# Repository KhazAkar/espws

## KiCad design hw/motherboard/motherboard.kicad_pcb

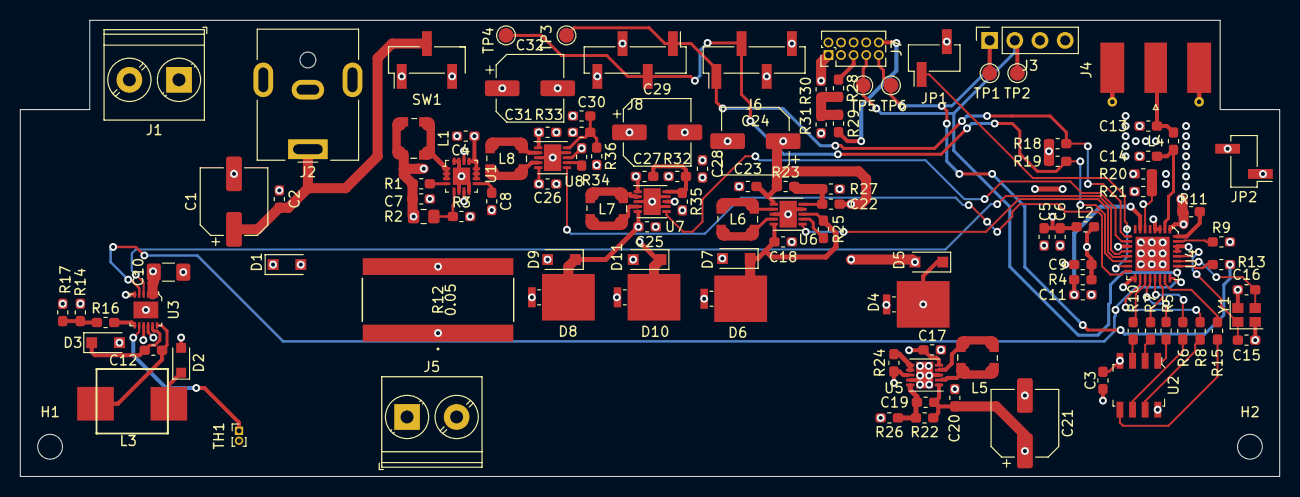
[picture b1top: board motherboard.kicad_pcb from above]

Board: 4 copper layers, 127.0 x 46.0 mm, 116 parts (0 on the bottom side), 75 nets.

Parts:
C1, C21, C24, C29, C32: 22uF; CP_Elec_6.3x5.4
C2, C3, C6, C11: 100nF; C_0603_1608Metric_Pad1.05x0.95mm_HandSolder
C4, C5: 10uF; C_0603_1608Metric_Pad1.05x0.95mm_HandSolder
C7, C17, C18, C25, C26: 22uF; C_0603_1608Metric_Pad1.05x0.95mm_HandSolder
C8: 680pF; C_0603_1608Metric_Pad1.05x0.95mm_HandSolder
C9, C20, C23, C28, C31: 1uF; C_0603_1608Metric_Pad1.05x0.95mm_HandSolder
C10: 22uF; C_1206_3216Metric_Pad1.42x1.75mm_HandSolder
C12: 1uF/50V; C_0603_1608Metric_Pad1.05x0.95mm_HandSolder
C13: 2.4pF; C_0603_1608Metric_Pad1.05x0.95mm_HandSolder
C14: 3pF; C_0603_1608Metric_Pad1.05x0.95mm_HandSolder
C15, C16: 10pF; C_0603_1608Metric_Pad1.05x0.95mm_HandSolder
C19, C27: 4.7uF; C_0603_1608Metric_Pad1.05x0.95mm_HandSolder
C22, C30: 47pF; C_0603_1608Metric_Pad1.05x0.95mm_HandSolder
D1, D3, D5, D7, D9, D11: DB2W40300L; D_SOD-123F
D2: CMDSH2-4L; D_SOD-323_HandSoldering
D4, D6, D8, D10: UPS115UE3; D_Powermite2_AK
H1, H2: MountingHole; MountingHole_2.5mm
J1: Solar Panel; TerminalBlock_Phoenix_PT-1,5-2-5.0-H_1x02_P5.00mm_Horizontal
J2: 9V 3A; BarrelJack_CUI_PJ-063AH_Horizontal
J3: ESP8266 UART; PinSocket_1x04_P2.54mm_Vertical
J4: WiFi Antenna; SMA_Molex_73251-1153_EdgeMount_Horizontal
J5: LiFePO4; TerminalBlock_Phoenix_PT-1,5-2-5.0-H_1x02_P5.00mm_Horizontal
J6: BME280; PinHeader_1x04_P2.54mm_Vertical_SMD_Pin1Left
J7: PMS7003; PinHeader_2x05_P1.27mm_Vertical
J8: WIND; PinHeader_1x04_P2.54mm_Vertical_SMD_Pin1Left
JP1: Programming mode; PinHeader_1x02_P2.54mm_Vertical_SMD_Pin1Left
JP2: Reset; PinHeader_1x02_P2.54mm_Vertical_SMD_Pin1Left
L1, L5, L6, L7, L8: 2.2uH; L_Wuerth_WE-TPC-3816
L2: 4.3nH; L_0603_1608Metric_Pad1.05x0.95mm_HandSolder
L3: 5.6uH; SRP6540
L4: 2.2nH; L_0603_1608Metric_Pad1.05x0.95mm_HandSolder
R1, R20, R26, R27, R35, R36: 100k; R_0603_1608Metric_Pad1.05x0.95mm_HandSolder
R2: 1M07; R_0805_2012Metric_Pad1.15x1.40mm_HandSolder
R3, R22, R32: 180k; R_0603_1608Metric_Pad1.05x0.95mm_HandSolder
R4, R11, R28, R29: 10k; R_0603_1608Metric_Pad1.05x0.95mm_HandSolder
R5, R6, R7, R8, R10, R15: 200; R_0603_1608Metric_Pad1.05x0.95mm_HandSolder
R9: 12k; R_0603_1608Metric_Pad1.05x0.95mm_HandSolder
R12: 0.05; FCSL150R050FER
R13: 499; R_0603_1608Metric_Pad1.05x0.95mm_HandSolder
R14: 30k; R_0603_1608Metric_Pad1.05x0.95mm_HandSolder
R16: 223k; R_0603_1608Metric_Pad1.05x0.95mm_HandSolder
R17: 330k; R_0603_1608Metric_Pad1.05x0.95mm_HandSolder
R18, R19, R31: 2k; R_0603_1608Metric_Pad1.05x0.95mm_HandSolder
R21: 37k; R_0603_1608Metric_Pad1.05x0.95mm_HandSolder
R23, R33: 150k; R_0603_1608Metric_Pad1.05x0.95mm_HandSolder
R24, R25, R34: 4.7k; R_0603_1608Metric_Pad1.05x0.95mm_HandSolder
R30: 1k; R_0603_1608Metric_Pad1.05x0.95mm_HandSolder
SW1: Charge/Power; PinHeader_1x03_P2.54mm_Vertical_SMD_Pin1Left
TH1: 10k B=3380; PinHeader_1x02_P1.00mm_Vertical
TP1: U0TXD_Test; TestPoint_Pad_D1.5mm
TP2: U0RXD_Test; TestPoint_Pad_D1.5mm
TP3: SCL_TP; TestPoint_Pad_D1.5mm
TP4: SDA_TP; TestPoint_Pad_D1.5mm
TP5: DUST_RX_TP; TestPoint_Pad_D1.5mm
TP6: DUST_TX_TP; TestPoint_Pad_D1.5mm
U1: TPS62140A; VFQFN-16-1EP_3x3mm
U2: GD25Q32CSIGR; SOIC-8_W5.3mm
U3: LT3652EDD; DFN-12-1EP_3x3mm
U4: ESP8266EX; QFN-32-1EP_5x5mm
U5, U6, U7, U8: RT6150; DFN-10-1EP_3x3mm_P0.5mm_EP1.75x2.7mm
Y1: 40MHz±10ppm; Crystal_SMD_2520-4Pin_2.5x2.0mm

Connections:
5V6: C7.1, D5.2, D7.2, D9.2, D11.2, L1.2, R1.1, R2.1, U1.7, U1.14
+9V: D1.2, SW1.1
+9VA: C4.1, SW1.3, U1.10, U1.11, U1.12, U1.13
+12V: C10.1, D1.1, J1.1, U3.1, U3.2, U3.3
+BATT: D3.2, D4.2, D6.2, D8.2, D10.2, J5.1, R12.1, R14.1, R20.1, U3.9
ADC: R20.2, R21.1, U4.6
BME280_EN: U4.10, U7.6
BME280_SCL: J6.1, J8.1, R18.2, TP3.1, U4.9
BME280_SDA: J6.2, J8.2, R19.2, TP4.1, U4.14
BME280_VCC: C27.1, C28.1, C29.1, J6.3, R32.1, U7.1
DUST_3V3: R28.2, R29.2, R30.2, R31.1
DUST_EN: U4.13, U6.6
DUST_RX: J3.2, J7.7, TP2.1, TP5.1, U4.25
DUST_TX: J3.1, J7.9, R13.1, TP1.1, TP6.1
DUST_VCC: C22.1, C23.1, C24.1, J7.1, J7.2, R23.1, R30.1, U6.1
ESP_VCC: C3.2, C5.1, C6.1, C9.1, C19.1, C20.1, C21.1, J3.3, JP2.2, L2.1, L2.2, R4.1, R11.2, R18.1, R19.1, R22.1, U2.8, U4.1, U4.3, U4.4, U4.11, U4.17, U4.29, U4.30, U5.1
GND: C1.2, C2.2, C3.1, C4.2, C5.2, C6.2, C7.2, C8.2, C9.2, C10.2, C11.2, C13.2, C14.2, C15.2, C16.2, C17.2, C18.2, C20.2, C21.2, C23.2, C24.2, C25.2, C26.2, C28.2, C29.2, C31.2, C32.2, D2.2, J1.2, J2.2, J3.4, J4.2, J5.2, J6.4, J7.3, J7.4, J8.4, JP1.2, JP2.1, R3.2, R9.2, R17.2, R21.2, R26.2, R27.2, R31.2, R35.2, R36.2, TH1.2, U1.6, U1.8, U1.15, U1.16, U1.17, U2.4, U3.6, U3.13, U4.33, U5.3, U5.9, U5.11, U6.3, U6.9, U6.11, U7.3, U7.7, U7.9, U7.11, U8.3, U8.9, U8.11, Y1.2, Y1.4
unnamed: C1.1, C2.1, J2.1, SW1.2
unnamed: C8.1, U1.9
unnamed: C11.1, R4.2, U4.7
unnamed: C12.1, L3.1, U3.12
unnamed: C12.2, D3.1, U3.11
unnamed: C13.1, J4.1, L4.1
unnamed: C14.1, L4.2, U4.2
unnamed: C15.1, U4.28, Y1.1
unnamed: C16.1, U4.27, Y1.3
unnamed: C17.1, D4.1, D5.1, R24.1, U5.5, U5.8
unnamed: C18.1, D6.1, D7.1, R25.1, U6.5, U6.8
unnamed: C19.2, R22.2, R26.1, U5.10
unnamed: C22.2, R23.2, R27.1, U6.10
unnamed: C25.1, D8.1, D9.1, U7.5, U7.8
unnamed: C26.1, D10.1, D11.1, R34.1, U8.5, U8.8
unnamed: C27.2, R32.2, R35.1, U7.10
unnamed: C30.2, R33.2, R36.1, U8.10
unnamed: D2.1, L3.2
unnamed: J7.5, R28.1
unnamed: J7.10, R29.1
unnamed: L1.1, U1.1, U1.2, U1.3
unnamed: L5.1, U5.2
unnamed: L5.2, U5.4
unnamed: L6.1, U6.2
unnamed: L6.2, U6.4
unnamed: L7.1, U7.2
unnamed: L7.2, U7.4
unnamed: L8.1, U8.2
unnamed: L8.2, U8.4
unnamed: R1.2, U1.4
unnamed: R2.2, R3.1, U1.5
unnamed: R5.2, U4.20
unnamed: R6.2, U4.21
unnamed: R7.2, U4.22
unnamed: R8.2, U4.18
unnamed: R9.1, U4.31
unnamed: R10.2, U4.19
unnamed: R11.1, U4.32
unnamed: R12.2, U3.10
unnamed: R13.2, U4.26
unnamed: R14.2, R16.1, R17.1
unnamed: R15.2, U4.23
unnamed: R16.2, U3.7
unnamed: R24.2, U5.6, U5.7
unnamed: R25.2, U6.7
unnamed: R34.2, U8.7
unnamed: TH1.1, U3.8
PRG: JP1.1, U4.15
SD_CLK: R6.1, U2.6
SD_CMD: R5.1, U2.1
SD_D0: R7.1, U2.2
SD_D1: R15.1, U2.5
SD_D2: R8.1, U2.7
SD_D3: R10.1, U2.3
WIND_EN: U4.16, U8.6
WIND_VCC: C30.1, C31.1, C32.1, J8.3, R33.1, U8.1
~CHARGE: U3.4, U4.12
~FAULT: U3.5, U4.24

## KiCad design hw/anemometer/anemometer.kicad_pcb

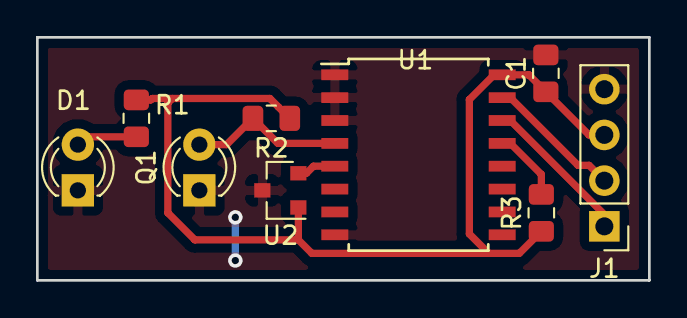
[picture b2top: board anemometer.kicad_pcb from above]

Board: 2 copper layers, 34.0 x 13.5 mm, 9 parts (0 on the bottom side), 8 nets.

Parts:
C1: 100nF; C_0805_2012Metric_Pad1.15x1.40mm_HandSolder
D1: TSAL4400; LED_D3.0mm_IRBlack
J1: Connector for motherboard; PinHeader_1x04_P2.54mm_Vertical
Q1: LL-304PTC4B-1AD; LED_D3.0mm_Clear
R1: 39; C_0805_2012Metric_Pad1.15x1.40mm_HandSolder
R2: 10k; C_0805_2012Metric_Pad1.15x1.40mm_HandSolder
R3: 2k; C_0805_2012Metric_Pad1.15x1.40mm_HandSolder
U1: PCF8574; SOIC-16W_7.5x10.3mm_P1.27mm
U2: SS360PT; SOT-23

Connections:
+3V3: C1.1, J1.3, R1.1, R2.1, R3.1, U1.16, U2.1
/HALL_OUT: U1.5, U2.2
/IR_OUT: Q1.2, R2.2, U1.4
GND: C1.2, D1.1, J1.4, Q1.1, U1.1, U1.2, U1.3, U1.8, U2.3
unnamed: D1.2, R1.2
unnamed: J1.1, U1.14
unnamed: J1.2, U1.15
unnamed: R3.2, U1.13

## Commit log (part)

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2018-11-19 Placeholder main.c file with code from blinky example from esp-open-sdk and slightly modified Makefile
2018-11-19 Update .gitignore file
2018-11-19 Add baudrate variable to esptool, change comment style and reformat main.c file
2018-11-19 KiCAD project placeholders
2018-11-19 Add concept and plans for the project
2018-11-19 Make makefile more configurable
2018-11-19 Fix typo in comment.
2018-11-19 Add hierarchical schematics to main motherboard schematic file.
2018-11-21 Add placeholder for 3D model, minor change in electronic schematics arragement.
2018-11-22 Little reorganisation of files + "full" esptool.py to flash image.
2018-11-22 Add license for whole project, except for esptool.py, which have it's own license.
2018-11-22 Clarify license situation.
2018-11-22 Added new functions to makefile and placeholders for additional drivers.
2018-11-22 Repair visibility of dot files.
2018-11-25 Make battery slot with real battery measurings + space for cable management and connectivity between battery and mainboard
2018-11-25 WIP with battery charger
2018-11-25 Add another module and placeholder for battery driver using ATTiny2313
2018-11-25 Fix in main Makefile and slight change in main.c file for ATTiny2313
2018-11-26 Minor changes here and there.
2018-11-26 Remove unnecessary wpa2 driver, add drivers for i2c and spi
2018-11-26 Change concept about hardware design.
2018-11-26 Slight change and my thoughts
2018-11-28 Little redesign and choose MCU for power supply/battery charger.
2018-11-28 Add placeholder code and change from battery driver to advanced power supply
2018-12-03 Start of writing custom Makefile, edit main.c and schematic for P.S
2018-12-03 Fix slight typo
2018-12-04 Add concept for power supply, edit some C files and try to debug.
2018-12-09 Custom libraries, power supply schematics changes, AVR code changes.
2018-12-22 HUUUUGE general changes, need to organise that crap.
2018-12-23 Slight changes to ESP Makefile
2019-01-06 Some random changes
2019-01-07 Add flash chip for ESP, little more work toward the end
2019-01-13 Still working on schematics, much closer to end.
2019-01-15 Mainly changing naming scheme for sensors and other components
2019-01-25 Total reorganization, complete redo of schematics
2019-01-27 Slight changes in schematics, added thesis folder for project.
2019-01-31 Start anemometer project, little add up to thesis and start of PCB.
2019-02-05 Fix miniorities in schematics, little more pcb element placement.
2019-02-05 Add test points for some measurements to troubleshoot circuit.
2019-02-05 Same update
2019-02-06 New update from new system (Debian)
2019-02-06 Test to repair that stupid EGit
2019-02-08 Cleanup in code, add libraries and cleanup footprints connections etc.
2019-02-08 Changes in code, added libraries and updated schematics a little.
2019-02-11 Add diagram(need to be updated) and schematic overhaul + new symbol.
2019-02-14 Custom footrpints, start of making PCB layout.
2019-02-14 First attempt to layout, fix in footprints a little
2019-02-16 Change outline and mounting holes to match Kradex Z4 enclosure
2019-02-18 More work on thesis and code, less on PCB
2019-02-19 Little more PCB routing + minor fixes to the thesis
2019-02-20 More PCB layout, hard AF,really
2019-02-23 PCB done, slight change in schematic.
2019-03-04 Archive footprints, create anemometer schematic and slight changes to the code.
2019-03-05 Update from new system - OpenSUSE Tumbleweed
2019-03-05 Rebuild thesis + change name in commits.
2019-03-06 Little update in thesis
2019-03-06 New file.
2019-03-12 HUGE update to the thesis and minor changes in gerbers
2019-03-14 Slight update to the thesis, still more to do.
2019-03-18 HUGE update to the thesis, re-do diagram, change from C SDK to Arduino.
2019-03-24 Add PDF Schematic
2019-03-24 Repair
2019-03-24 HUGE update to the thesis, add PDF schematic and more!
2019-03-26 Mayby repaired that git this time.
2019-03-28 Near 50% of code, thesis near complete. Unfortunately not complete :(
2019-03-29 Practically working, thesis written, yay!
2019-04-04 Little changes
2019-04-04 Add presentation

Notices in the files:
parts and their libraries:
Copyright 2016 Accelerated Designs. All rights reserved.
